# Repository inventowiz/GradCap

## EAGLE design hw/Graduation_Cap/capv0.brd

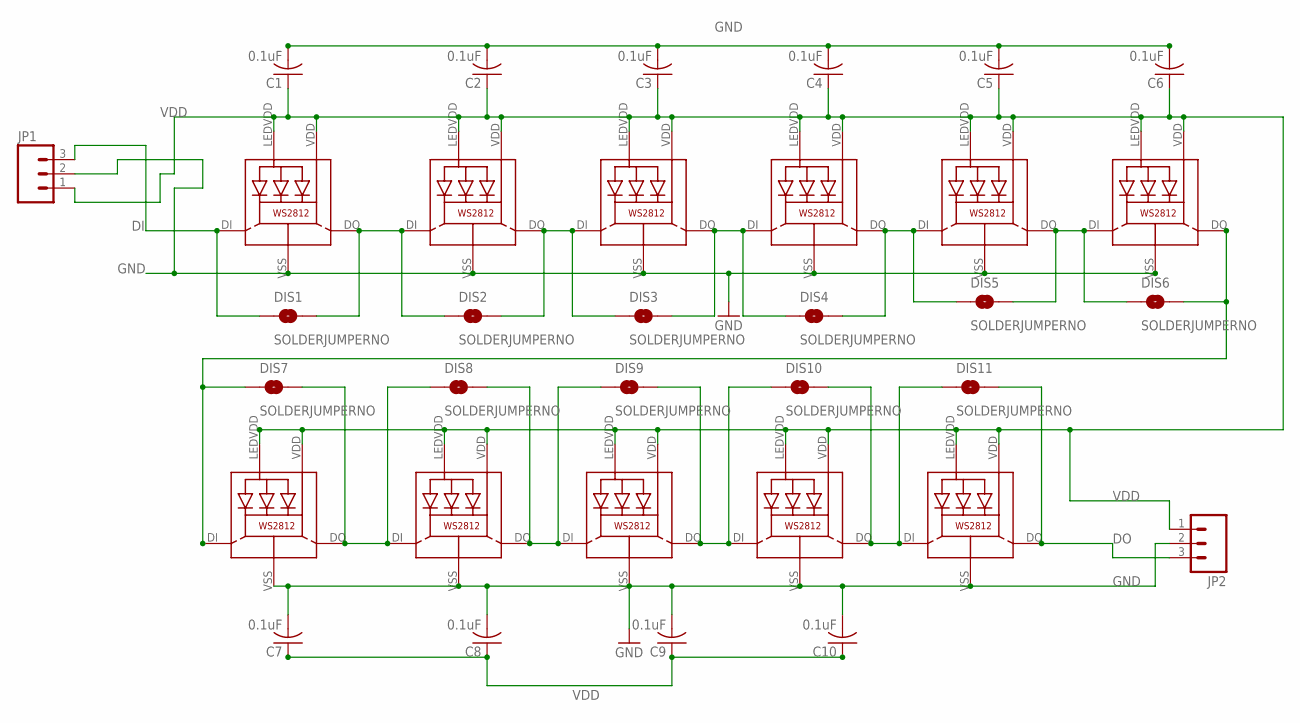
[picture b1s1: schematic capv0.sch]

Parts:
C1, C2, C3, C4, C5, C6, C7, C8, C9, C10: 0.1uF; C0805
DIS1, DIS2, DIS3, DIS4, DIS5, DIS6, DIS7, DIS8, DIS9, DIS10, DIS11: SOLDERJUMPERNO; SJ_2S-NO
JP1, JP2: M03LOCK; 1X03_LOCK
LED1, LED2, LED3, LED4, LED5, LED6, LED7, LED8, LED9, LED10, LED11: WS2812

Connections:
DI: DIS1.1, JP1.3, LED1.DI
DO: DIS11.2, JP2.3, LED11.DO
GND: C1.2, C2.2, C3.2, C4.2, C5.2, C6.2, C7.2, C8.2, C9.2, C10.2, JP1.2, JP2.2, LED1.VSS (GND), LED2.VSS (GND), LED3.VSS (GND), LED4.VSS (GND), LED5.VSS (GND), LED6.VSS (GND), LED7.VSS (GND), LED8.VSS (GND), LED9.VSS (GND), LED10.VSS (GND), LED11.VSS (GND)
unnamed: DIS1.2, DIS2.1, LED1.DO, LED2.DI
unnamed: DIS2.2, DIS3.1, LED2.DO, LED3.DI
unnamed: DIS3.2, DIS4.1, LED3.DO, LED4.DI
unnamed: DIS4.2, DIS5.1, LED4.DO, LED5.DI
unnamed: DIS5.2, DIS6.1, LED5.DO, LED6.DI
unnamed: DIS6.2, DIS7.1, LED6.DO, LED7.DI
unnamed: DIS7.2, DIS8.1, LED7.DO, LED8.DI
unnamed: DIS8.2, DIS9.1, LED8.DO, LED9.DI
unnamed: DIS9.2, DIS10.1, LED9.DO, LED10.DI
unnamed: DIS10.2, DIS11.1, LED10.DO, LED11.DI
VDD: C1.1, C2.1, C3.1, C4.1, C5.1, C6.1, C7.1, C8.1, C9.1, C10.1, JP1.1, JP2.1, LED1.LEDVDD, LED1.VDD, LED2.LEDVDD, LED2.VDD, LED3.LEDVDD, LED3.VDD, LED4.LEDVDD, LED4.VDD, LED5.LEDVDD, LED5.VDD, LED6.LEDVDD, LED6.VDD, LED7.LEDVDD, LED7.VDD, LED8.LEDVDD, LED8.VDD, LED9.LEDVDD, LED9.VDD, LED10.LEDVDD, LED10.VDD, LED11.LEDVDD, LED11.VDD

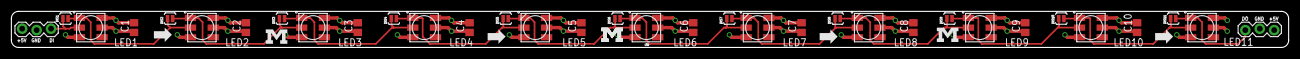
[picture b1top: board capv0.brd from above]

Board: 2 copper layers, 224.8 x 6.3 mm, 34 parts (0 on the bottom side), 14 nets.

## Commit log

2020-05-30 initial commit of old project
2020-06-02 first draft of changes for jonathan

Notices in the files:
parts and their libraries:
SparkFun-Connectors: Licensing: CC v3.0 Share-Alike You are welcome to use this library for commercial purposes.
